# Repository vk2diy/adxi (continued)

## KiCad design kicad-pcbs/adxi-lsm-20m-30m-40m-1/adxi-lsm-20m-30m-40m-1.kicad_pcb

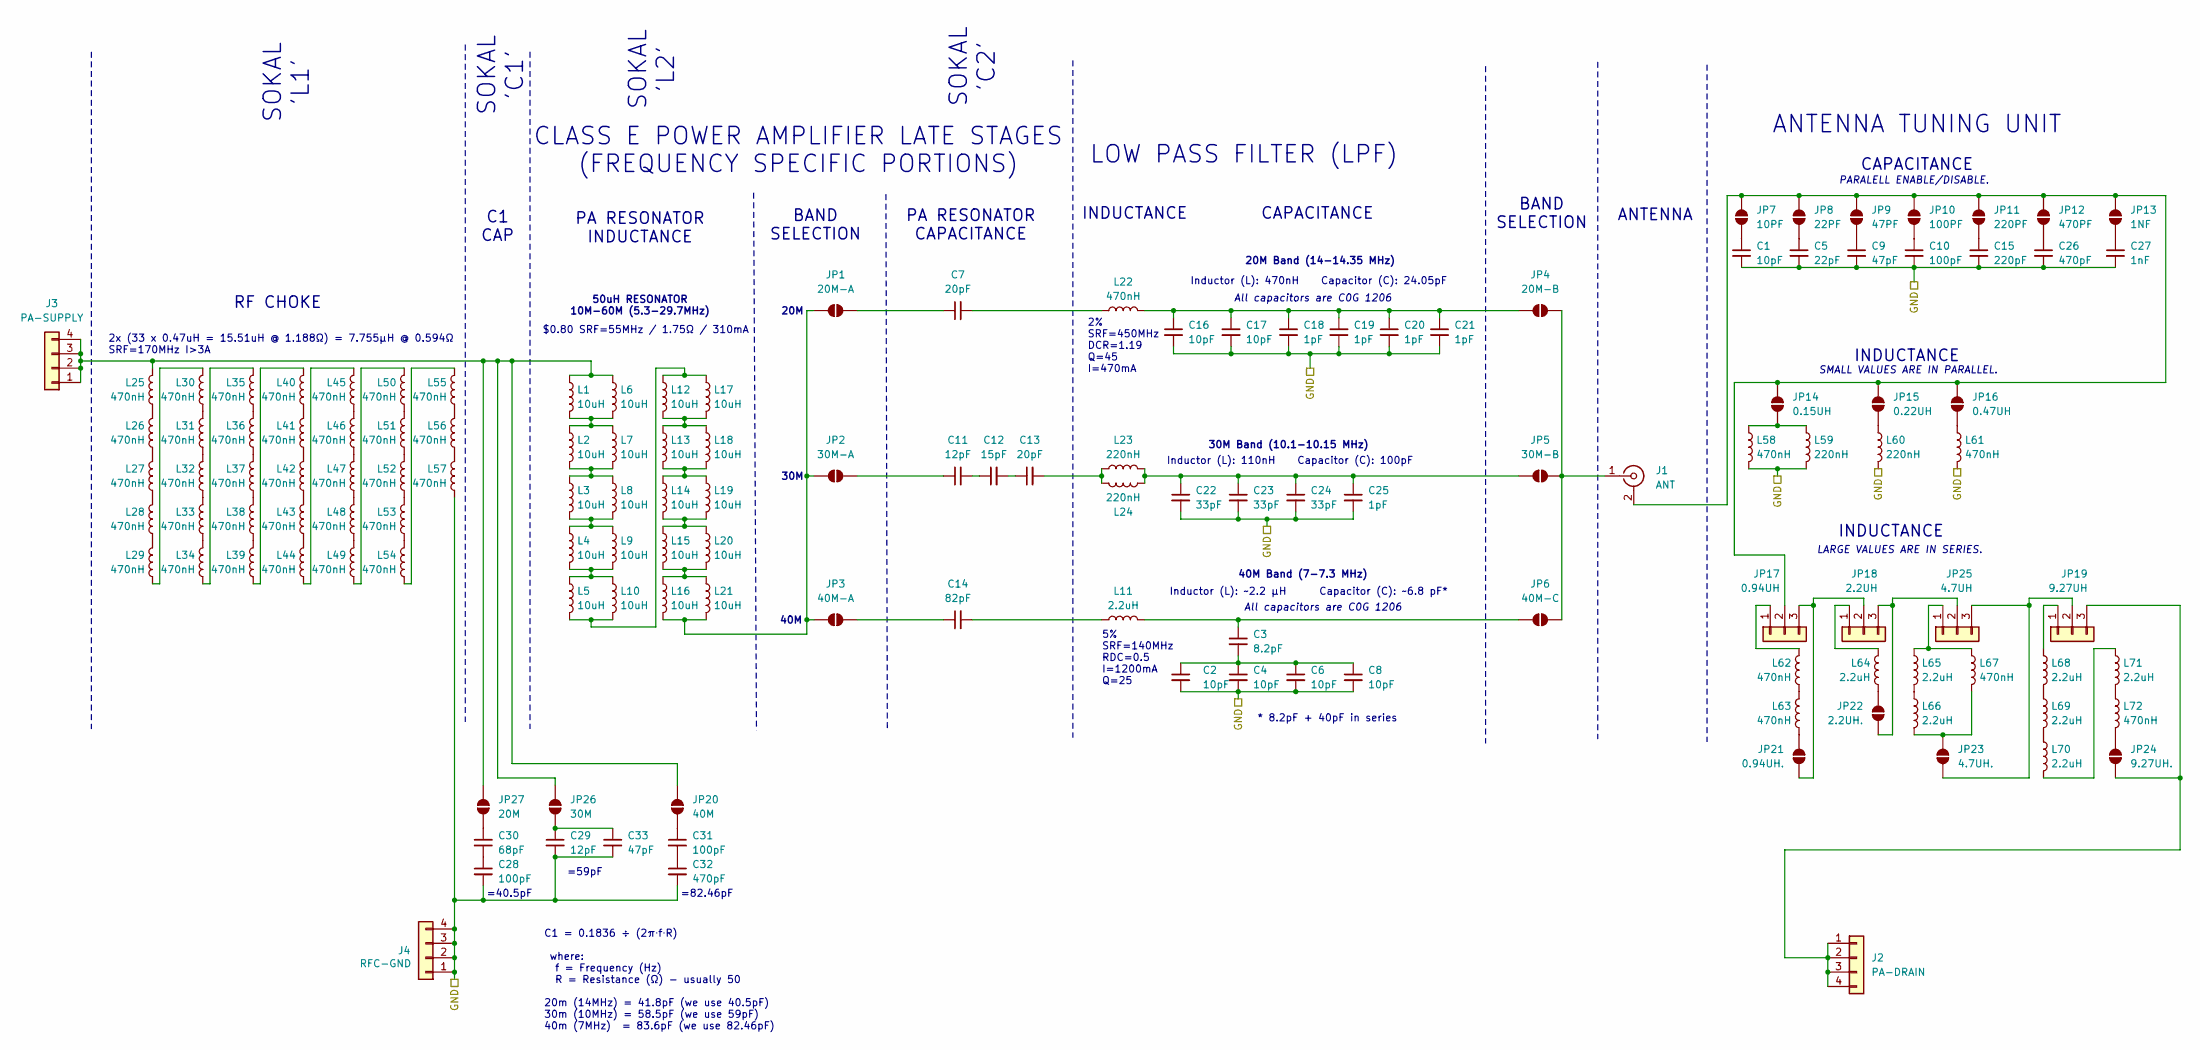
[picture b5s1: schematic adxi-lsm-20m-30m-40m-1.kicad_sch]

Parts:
C1: 10pF; C_0603_1608Metric; MPN CL10C100JB8NNNC; LCSC Part # C1634
C2, C4, C6, C8, C16, C17: 10pF; C_1206_3216Metric; MPN TCC1206COG100J102DT; LCSC Part # C377014
C3: 8.2pF; C_1206_3216Metric; MPN 1206CG8R2C500NT; LCSC Part # C3037650
C5: 22pF; C_0805_2012Metric; MPN CL21C220JBANNNC; LCSC Part # C1804
C7, C13: 20pF; C_1206_3216Metric; MPN 1206CG200J500NT; LCSC Part # C1894
C9, C33: 47pF; C_0805_2012Metric; MPN CL21C470JBANNNC; LCSC Part # C14857
C10, C28, C31: 100pF; C_0805_2012Metric; MPN CL21C101JBANNNC; LCSC Part # C1790
C11: 12pF; C_1206_3216Metric; MPN 1206CG120J500NT; LCSC Part # C1886
C12: 15pF; C_1206_3216Metric; MPN 1206CG150J500NT; LCSC Part # C1887
C14: 82pF; C_1206_3216Metric; MPN TCC1206COG820J500DT; LCSC Part # C282806
C15: 220pF; C_0805_2012Metric; MPN CC0805KRX7R9BB221; LCSC Part # C107145
C18, C19, C20, C21, C25: 1pF; C_1206_3216Metric; MPN 1206CG1R0C500NT; LCSC Part # C1891
C22, C23, C24: 33pF; C_1206_3216Metric; MPN GRM31A5C2J330JW01D; LCSC Part # C415521
C26, C32: 470pF; C_0805_2012Metric; MPN 0805B471K500NT; LCSC Part # C1743
C27: 1nF; C_1206_3216Metric; MPN 1206B102K202NT; LCSC Part # C9196
C29: 12pF; C_0603_1608Metric; MPN CL10C120JB8NNNC; LCSC Part # C38523
C30: 68pF; C_0603_1608Metric; MPN CL10C680JB8NNNC; LCSC Part # C28262
J1: ANT; ANT-TH_KH-BNC50-3511
J2: PA-DRAIN; PinSocket_1x04_P2.54mm_Vertical
J3: PA-SUPPLY; PinSocket_1x04_P2.54mm_Vertical
J4: RFC-GND; PinSocket_1x04_P2.54mm_Vertical
JP1: 20M-A; SolderJumper-2_P1.3mm_Open_RoundedPad1.0x1.5mm
JP2: 30M-A; SolderJumper-2_P1.3mm_Open_RoundedPad1.0x1.5mm
JP3: 40M-A; SolderJumper-2_P1.3mm_Open_RoundedPad1.0x1.5mm
JP4: 20M-B; SolderJumper-2_P1.3mm_Open_RoundedPad1.0x1.5mm
JP5: 30M-B; SolderJumper-2_P1.3mm_Open_RoundedPad1.0x1.5mm
JP6: 40M-C; SolderJumper-2_P1.3mm_Open_RoundedPad1.0x1.5mm
JP7: 10PF; SolderJumper-2_P1.3mm_Open_RoundedPad1.0x1.5mm
JP8: 22PF; SolderJumper-2_P1.3mm_Open_RoundedPad1.0x1.5mm
JP9: 47PF; SolderJumper-2_P1.3mm_Open_RoundedPad1.0x1.5mm
JP10: 100PF; SolderJumper-2_P1.3mm_Open_RoundedPad1.0x1.5mm
JP11: 220PF; SolderJumper-2_P1.3mm_Open_RoundedPad1.0x1.5mm
JP12: 470PF; SolderJumper-2_P1.3mm_Open_RoundedPad1.0x1.5mm
JP13: 1NF; SolderJumper-2_P1.3mm_Open_RoundedPad1.0x1.5mm
JP14: 0.15UH; SolderJumper-2_P1.3mm_Open_RoundedPad1.0x1.5mm
JP15: 0.22UH; SolderJumper-2_P1.3mm_Open_RoundedPad1.0x1.5mm
JP16: 0.47UH; SolderJumper-2_P1.3mm_Open_RoundedPad1.0x1.5mm
JP17: 0.94UH; PinHeader_1x03_P1.00mm_Vertical
JP18: 2.2UH; PinHeader_1x03_P1.00mm_Vertical
JP19: 9.27UH; PinHeader_1x03_P1.00mm_Vertical
JP20: 40M; SolderJumper-2_P1.3mm_Open_RoundedPad1.0x1.5mm
JP21: 0.94UH.; SolderJumper-2_P1.3mm_Open_RoundedPad1.0x1.5mm
JP22: 2.2UH.; SolderJumper-2_P1.3mm_Open_RoundedPad1.0x1.5mm
JP23: 4.7UH.; SolderJumper-2_P1.3mm_Open_RoundedPad1.0x1.5mm
JP24: 9.27UH.; SolderJumper-2_P1.3mm_Open_RoundedPad1.0x1.5mm
JP25: 4.7UH; PinHeader_1x03_P1.00mm_Vertical
JP26: 30M; SolderJumper-2_P1.3mm_Open_RoundedPad1.0x1.5mm
JP27: 20M; SolderJumper-2_P1.3mm_Open_RoundedPad1.0x1.5mm
L1, L2, L3, L4, L5, L6, L7, L8, L9, L10, L12, L13, L14, L15, L16, L17, L18, L19, L20, L21: 10uH; L_1008_2520Metric; MPN NLV25T-100J-PF; LCSC Part # C76825
L11, L64, L65, L66, L68, L69, L70, L71: 2.2uH; L_Chilisin_NLC252018-2.92x2.50x2.20; MPN NLC252018T-2R2J-N; LCSC Part # C285674
L22, L58, L61, L62, L63, L67, L72: 470nH; L_1008_2520Metric; MPN FEC1008CP-R47G-LRH; LCSC Part # C346450
L23, L24, L59, L60: 220nH; L_0805_2012Metric; MPN FHW0805UCR22JGT; LCSC Part # C108960
L25, L26, L27, L28, L29, L30, L31, L32, L33, L34, L35, L36, L37, L38, L39, L40, L41, L42, L43, L44, L45, L46, L47, L48, L49, L50, L51, L52, L53, L54, L55, L56, L57: 470nH; L_1008_2520Metric; MPN SPH252012HR47MT; LCSC Part # C316369

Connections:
/GND: C1.2, C2.2, C4.2, C5.2, C6.2, C8.2, C9.2, C10.2, C15.2, C16.2, C17.2, C18.2, C19.2, C20.2, C21.2, C22.2, C23.2, C24.2, C25.2, C26.2, C27.2, C28.2, C29.2, C32.2, C33.2, J4.1, J4.2, J4.3, J4.4, L57.2, L58.2, L59.2, L60.2, L61.2
unnamed: C2.1, C3.2, C4.1, C6.1, C8.1
unnamed: C7.2, L22.1
unnamed: C11.2, C12.1
unnamed: C12.2, C13.1
unnamed: C13.2, L23.1, L24.1
unnamed: C14.2, L11.1
unnamed: C28.1, C30.2
unnamed: C31.2, C32.1
unnamed: J1.2 (Ext), JP7.1 (A), JP8.1 (A), JP9.1 (A), JP10.1 (A), JP11.1 (A), JP12.1 (A), JP13.1 (A), JP14.1 (A), JP15.1 (A), JP16.1 (A), JP17.2
unnamed: J1.1 (In), JP4.2 (B), JP5.2 (B), JP6.2 (B)
unnamed: J2.1, J2.2, J2.3, J2.4, JP19.3, JP24.2 (B)
unnamed: J3.1, J3.2, J3.3, J3.4, JP20.2 (B), JP26.2 (B), JP27.2 (B), L1.1, L6.1, L25.1
unnamed: JP1.1 (A), JP2.1 (A), JP3.1 (A), L16.2, L21.2
unnamed: C7.1, JP1.2 (B)
unnamed: C11.1, JP2.2 (B)
unnamed: C14.1, JP3.2 (B)
unnamed: C16.1, C17.1, C18.1, C19.1, C20.1, C21.1, JP4.1 (A), L22.2
unnamed: C22.1, C23.1, C24.1, C25.1, JP5.1 (A), L23.2, L24.2
unnamed: C3.1, JP6.1 (A), L11.2
unnamed: C1.1, JP7.2 (B)
unnamed: C5.1, JP8.2 (B)
unnamed: C9.1, JP9.2 (B)
unnamed: C10.1, JP10.2 (B)
unnamed: C15.1, JP11.2 (B)
unnamed: C26.1, JP12.2 (B)
unnamed: C27.1, JP13.2 (B)
unnamed: JP14.2 (B), L58.1, L59.1
unnamed: JP15.2 (B), L60.1
unnamed: JP16.2 (B), L61.1
unnamed: JP17.1, L62.1
unnamed: JP17.3, JP18.2, JP21.2 (B)
unnamed: JP18.1, L64.1
unnamed: JP18.3, JP22.2 (B), JP25.2
unnamed: JP19.1, L68.1
unnamed: JP19.2, JP23.2 (B), JP25.3
unnamed: C31.1, JP20.1 (A)
unnamed: JP21.1 (A), L63.2
unnamed: JP22.1 (A), L64.2
unnamed: JP23.1 (A), L66.2, L67.2
unnamed: JP24.1 (A), L72.2
unnamed: JP25.1, L65.1, L67.1
unnamed: C29.1, C33.1, JP26.1 (A)
unnamed: C30.1, JP27.1 (A)
unnamed: L1.2, L2.1, L6.2, L7.1
unnamed: L2.2, L3.1, L7.2, L8.1
unnamed: L3.2, L4.1, L8.2, L9.1
unnamed: L4.2, L5.1, L9.2, L10.1
unnamed: L5.2, L10.2, L12.1, L17.1
unnamed: L12.2, L13.1, L17.2, L18.1
unnamed: L13.2, L14.1, L18.2, L19.1
unnamed: L14.2, L15.1, L19.2, L20.1
unnamed: L15.2, L16.1, L20.2, L21.1
unnamed: L25.2, L26.1
unnamed: L26.2, L27.1
unnamed: L27.2, L28.1
unnamed: L28.2, L29.1
unnamed: L29.2, L30.1
unnamed: L30.2, L31.1
unnamed: L31.2, L32.1
unnamed: L32.2, L33.1
unnamed: L33.2, L34.1
unnamed: L34.2, L35.1
unnamed: L35.2, L36.1
unnamed: L36.2, L37.1
unnamed: L37.2, L38.1
unnamed: L38.2, L39.1
unnamed: L39.2, L40.1
unnamed: L40.2, L41.1
unnamed: L41.2, L42.1
unnamed: L42.2, L43.1
unnamed: L43.2, L44.1
unnamed: L44.2, L45.1
unnamed: L45.2, L46.1
unnamed: L46.2, L47.1
unnamed: L47.2, L48.1
unnamed: L48.2, L49.1
unnamed: L49.2, L50.1
unnamed: L50.2, L51.1
unnamed: L51.2, L52.1
unnamed: L52.2, L53.1
unnamed: L53.2, L54.1
unnamed: L54.2, L55.1
unnamed: L55.2, L56.1
unnamed: L56.2, L57.1
unnamed: L62.2, L63.1
unnamed: L65.2, L66.1
unnamed: L68.2, L69.1
unnamed: L69.2, L70.1
unnamed: L70.2, L71.1
unnamed: L71.2, L72.1

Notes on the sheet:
RF CHOKE
50uH RESONATOR 10M-60M (5.3-29.7MHz)
INDUCTANCE
40M
CAPACITANCE
ANTENNA
Inductor (L): 470nH Capacitor (C): 24.05pF
20M Band (14-14.35 MHz)
=40.5pF
All capacitors are C0G 1206
SMALL VALUES ARE IN PARALLEL.
40M Band (7-7.3 MHz)
Inductor (L): ~2.2 μH Capacitor (C): ~6.8 pF*
Inductor (L): 110nH Capacitor (C): 100pF
PARALELL ENABLE/DISABLE.
5% SRF=140MHz RDC=0.5 I=1200mA Q=25
C1 = 0.1836 ÷ (2π⋅f⋅R) where: f = Frequency (Hz) R = Resistance (Ω) - usually 50 20m (14MHz) = 41.8pF (we use 40.5pF) 30m (10MHz) = 58.5pF (we use 59pF) 40m (7MHz) = 83.6pF (we use 82.46pF)
LOW PASS FILTER (LPF)
ANTENNA TUNING UNIT
2x (33 x 0.47uH = 15.51uH @ 1.188Ω) = 7.755μH @ 0.594Ω SRF=170MHz I>3A
=82.46pF
C1 CAP
SOKAL 'C2'
$0.80 SRF=55MHz / 1.75Ω / 310mA
BAND SELECTION
30M Band (10.1-10.15 MHz)
LARGE VALUES ARE IN SERIES.
* 8.2pF + 40pF in series
SOKAL 'L1'
PA RESONATOR INDUCTANCE
2% SRF=450MHz DCR=1.19 Q=45 I=470mA
SOKAL 'L2'
20M
CLASS E POWER AMPLIFIER LATE STAGES (FREQUENCY SPECIFIC PORTIONS)
SOKAL 'C1'
=59pF
30M
PA RESONATOR CAPACITANCE

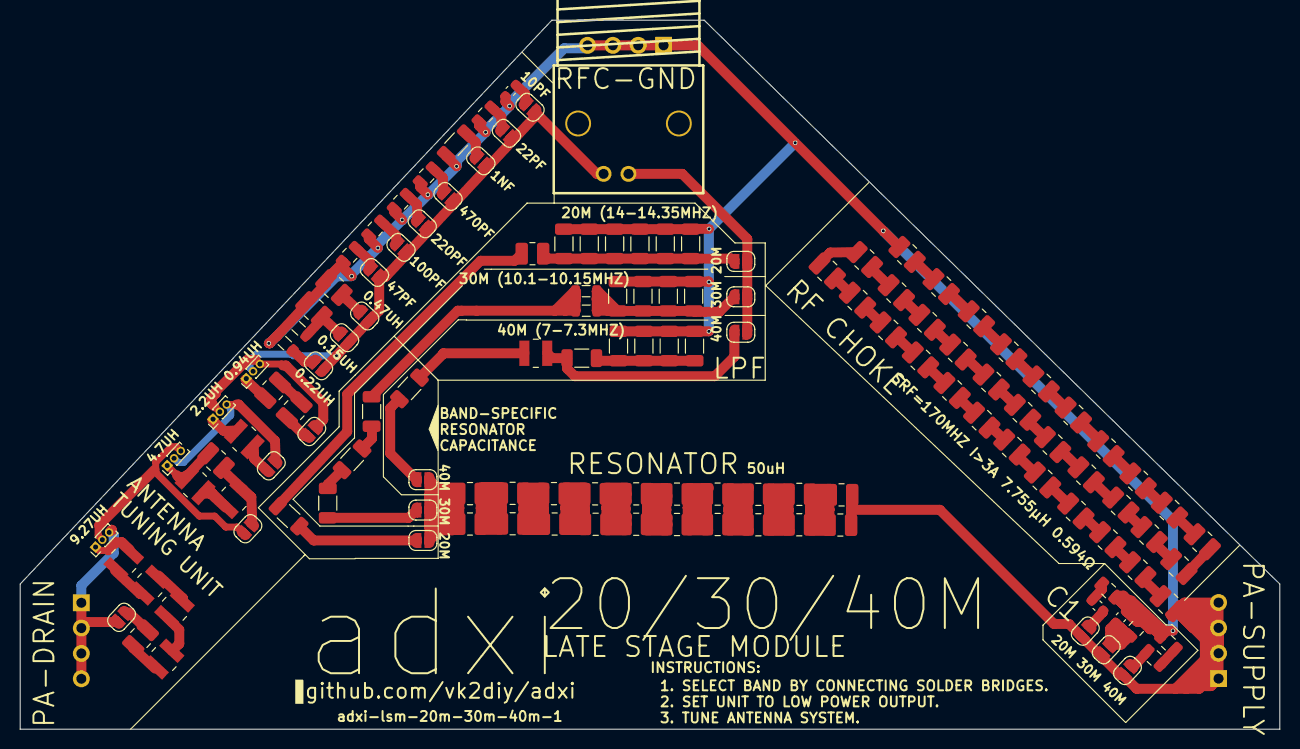
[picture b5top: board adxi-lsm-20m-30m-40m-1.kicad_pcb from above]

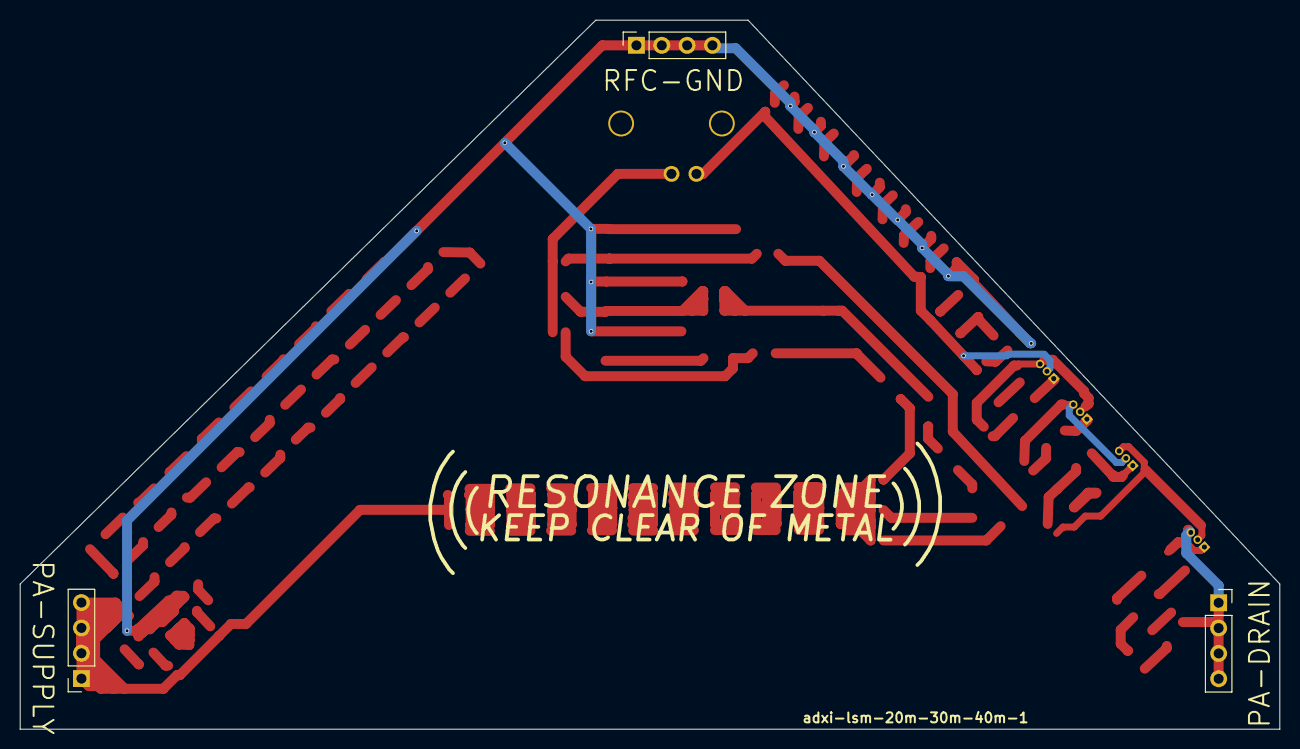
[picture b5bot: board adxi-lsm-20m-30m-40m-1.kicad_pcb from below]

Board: 2 copper layers, 126.3 x 71.1 mm, 136 parts (3 on the bottom side), 91 nets.

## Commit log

2024-08-03 Initial cleanup
2024-08-03 Unify contributors
2024-08-03 Tweak instruction
2024-08-03 Status
2024-08-03 Further update
2024-08-03 Further notes
2024-08-03 Further notes and trajectory
2024-08-07 Revised board in progress
2024-08-07 Draft PCB
2024-08-07 Reading
2024-08-07 LPF notes
2024-08-07 Plans
2024-08-07 Input filter model
2024-08-07 Bandpass filter model
2024-08-07 Further documentation
2024-08-07 SWR notes
2024-08-07 Ignore backups and caches
2024-08-07 DC blocking filter
2024-08-07 Simplify fork focus statement
2024-08-07 Protocol documentation
2024-08-07 protocols
2024-08-07 Add link for contributor
2024-08-07 Contributor URLs
2024-08-08 More theory!
2024-08-09 LPFs, footprints, component selection, switching
2024-08-09 More bands
2024-08-09 Updated draft
2024-08-09 Antenna tuning
2024-08-09 More on ATUs
2024-08-09 PhDness
2024-08-09 more notes
2024-08-13 Improve intro
2024-08-14 Notes
2024-08-14 more
2024-08-14 redorder
2024-08-14 better
2024-08-14 better output filename
2024-08-14 neater output
2024-08-14 ignore downloaded files
2024-08-14 Working inductor array
2024-08-14 SRF OK
2024-08-14 Final update for today
2024-08-15 Fix dates
2024-08-17 Better file name
2024-08-17 Progress?
2024-08-18 More outputs, etc
2024-08-18 Aha!
2024-08-18 RF choke for 70cm
2024-08-18 Closer to functional PA
2024-08-19 Further PA choke work
2024-08-19 Abbreviation
2024-08-19 Pluggable PA module
2024-08-19 Pluggable PAs
2024-08-20 Module proposal
2024-08-20 Layer diagram
2024-08-20 Revised diagram
2024-08-20 Conclusions
2024-08-20 Rationalize
2024-08-20 Source of error
2024-08-21 Cypress option
2024-08-21 Significant updates
2024-08-22 Toward one USB cable
2024-08-22 Audio summing theory
2024-08-23 New footprints and 3D models
2024-08-23 USB work
2024-08-26 PSU documentation
2024-08-26 SPI level conversion
2024-08-26 USB hub
2024-08-26 News
2024-08-26 Another model
2024-08-27 Model switching harmonics
2024-08-27 Improve status
2024-08-27 More on USB PD
2024-08-27 More audio summing
2024-08-29 More MCU detail
2024-08-29 Datasheet
2024-08-29 Audio chipset
2024-09-01 Receiver
2024-09-01 Better comparison model
2024-09-01 Improvements to receiver
2024-09-01 Corrected model
2024-09-01 Fixed
2024-09-02 More work, getting close now!
2024-09-02 Fix high numbered shield pins
2024-09-02 Official footprint with shared drain pin, SMT type and courtyard added
2024-09-02 Inductor
2024-09-02 Simplify PSU, add 4xM3 mounting holes, silkscreen, better footprints
2024-09-02 Notes on recent updates
2024-09-02 Update docs to match revised simplified PSU schematic
2024-09-02 Layout complete
2024-09-03 Fixed vias
2024-09-03 move schematics out of board
2024-09-03 Cleanup
2024-09-03 Add extra silkscreen
2024-09-03 Minor changes only
2024-09-03 More status update
2024-09-03 Minor silkscreen updates
2024-09-03 More status
2024-09-03 First late-stage module band selection
2024-09-03 typo
2024-09-03 Move images to subdirectory
2024-09-04 More symbols/footprints
2024-09-04 LSM prototype
2024-09-04 Prototype LSM
2024-09-05 20m/30m/40m late stage module
2024-09-05 Syntax fix
2024-09-07 Review
2024-09-10 Formatting
2024-09-10 Next steps
2024-09-17 Diode selection
2024-09-17 syntax
2024-10-23 Final board
2024-10-23 final
2024-10-23 Timeline
2024-10-23 Fix image paths
2024-10-24 Fix 150pF 0603 footprint incorrectly specified as 0201
2024-10-26 Move old files out of the way
2024-10-26 Remove swapfile
2024-10-26 Update footprint
2024-10-26 Commit outstanding files related to Kicad v8 updates
2024-10-26 Outstanding v8 upgrade changes
2024-10-26 Quiet
2024-11-05 Debugging
2024-11-05 Detail
2024-11-05 Remove old text
2024-11-06 More theory
2024-11-06 Debugging progress
2024-11-06 Fix path
2024-11-06 Path fix
2024-11-07 Fixes
2024-11-08 Today
2024-11-08 pathfix
2024-11-09 Further debugging
2024-11-09 Update notes
2024-11-10 Powerfix
2024-11-10 Relocate old builds and source files
2024-11-10 Ignore python venv files
2024-11-10 More issues
2024-11-10 Beginnings
2024-11-10 Better status
2024-11-10 Add analog comparator note; more explicit net names
2024-11-10 Better intro
2024-11-11 Innit!
2024-11-11 3V3 output pin name
2024-11-11 Explicit pin names
2024-11-18 Debugged!
2024-11-18 Add firmware documentation
2024-11-19 Working upload
2024-11-19 Working uploads
2024-11-19 Upload command
2024-11-19 Faster upload; disable verification
2024-11-19 Test firmware
2024-11-19 Improved test firmware
2024-11-19 Remove LFs
2024-11-22 More details
2024-11-22 First WSJT
2024-11-23 Debug
2024-11-23 Working
2024-11-24 Test routine; correct clock chip init; better variable names; RX/TX enable/disable; debugging; silence redef warnings
2024-11-24 Test harness
2024-11-24 Ethereal
2024-11-24 Development
2024-11-24 Histoire
2024-12-03 .plan
2024-12-03 Verify RXEN, etc.
2025-01-18 Antenna build
2025-01-18 More antenna goodness
2025-01-18 lengths
2025-01-18 Updated test plan
2025-01-23 Fancy pants
2025-01-27 LPF test
2025-01-27 Interpretation
2025-02-12 CD2003 vs direct sampling
